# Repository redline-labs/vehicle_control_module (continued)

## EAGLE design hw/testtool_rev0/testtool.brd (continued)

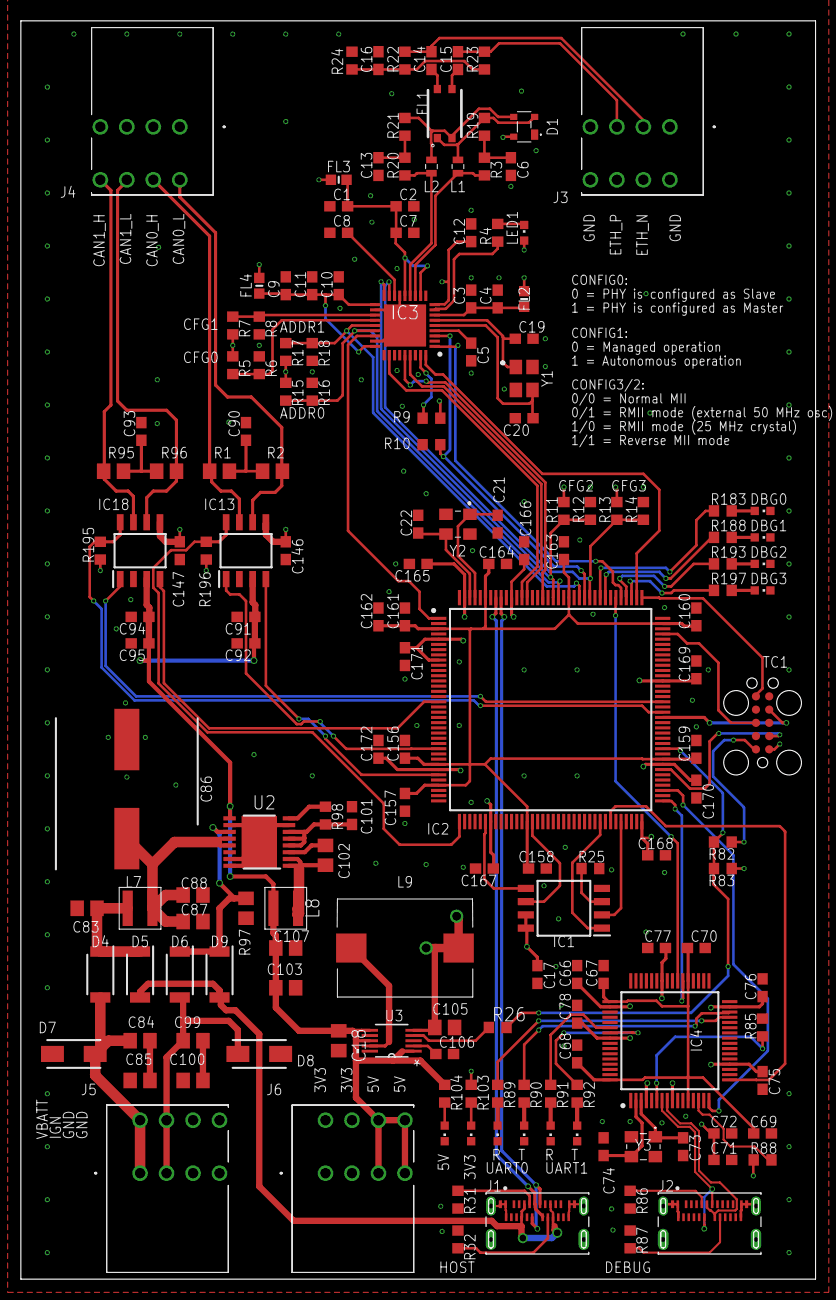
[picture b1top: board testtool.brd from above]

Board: 4 copper layers, 76.2 x 120.6 mm, 169 parts (0 on the bottom side), 113 nets.

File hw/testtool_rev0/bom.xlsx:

Parts | Qty | Value | Package | Device | Description | MANUFACTURER_NAME | MANUFACTURER_PART_NUMBER | MOUSER_PART_NUMBER
C1, C3, C9, C92, C95 | 5 | 10uF | C0603 | GRM188R6YA106MA73J | CAPACITOR, American symbol
C101 | 1 | 0.47uF | C0603 | C1608X7R1H474K080AC | CAPACITOR, American symbol
C102 | 1 | 220nF | C0805 | C0805X223K1RECAUTO | CAPACITOR, American symbol
C16, C90, C93 | 3 | 4.7nF | C0603 | C1608C0G2A472J080AE | CAPACITOR, American symbol
C18, C87, C103, C105, C107 | 5 | 10uF | C0805 | GRM21BC8YA106ME11L | CAPACITOR, American symbol
C19, C20 | 2 | 8.2pF | C0603 | GCM1885C2A8R2DA16D | CAPACITOR, American symbol
C2, C7, C10, C11, C14, C15, C17, C66, C68, C69, C70, C75, C76, C77, C78, C91, C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 | 34 | 100nF | C0603 | GCM1887U1H103JA16J | CAPACITOR, American symbol
C21, C22 | 2 | 12pF | C0603 | C0603C120K5GACTU | CAPACITOR, American symbol
C4, C5, C8, C12, C106, C162 | 6 | 1uF | C0603 | GMJ107CB7105MAHR | CAPACITOR, American symbol
C6, C13 | 2 | 47pF | C0603 | C0603C470J1GACAUTO | CAPACITOR, American symbol
C67 | 1 | 3.3uF | C0603 | C1608X5R1V335M080AC | CAPACITOR, American symbol
C71, C72, C165 | 3 | 4.7uF | C0603 | C1608JB1V475K080AC | CAPACITOR, American symbol
C73, C74 | 2 | 18nF | C0603 | GCM188R72A183KA37J | CAPACITOR, American symbol
C83, C88 | 2 | 0.47uF | C0805 | GCM21BR71H474KA55K | CAPACITOR, American symbol
C84, C85, C99, C100 | 4 | 470pF | C0805 | GCM21A5C2E471JX01D | CAPACITOR, American symbol
C86 | 1 | UCZ1K151MNQ1MS | CAPAE1360X1450N | UCZ1K151MNQ1MS | Aluminum Electrolytic Capacitors - SMD 80V 150UF 20% | Nichicon | UCZ1K151MNQ1MS | 647-UCZ1K151MNQ1MS
D1 | 1 | PESD2ETH-AXR | PESD2ETHAXR | PESD2ETH-AXR | ESD Suppressors / TVS Diodes PESD2ETH-AX/SOT4/REEL 7 Q3/T4" | Nexperia | PESD2ETH-AXR | 771-PESD2ETH-AXR
D4, D5, D6, D9 | 4 | PMEG3030EP,115 | SODFL4725X110N | PMEG3030EP,115 | Nexperia PMEG3030EP,115 SMT Schottky Diode, 30V 3A, 2-Pin SOD128 | Nexperia | PMEG3030EP,115 | 771-PMEG3030EP115
D7, D8 | 2 | SMAJ24CA-Q | DIONM5127X229N | SMAJ24CA-Q | Bourns SMAJ24CA-Q, Bi-Directional TVS Diode, 400W, 2-Pin DO-214AC | Bourns | SMAJ24CA-Q | 652-SMAJ24CA-Q
FL1 | 1 | ACT45L-201-2P-TL000 | ACT45L_1 | ACT45L-201-2P-TL000 | Common mode choke SMD 200uH 100mA 50V TDK ACT Series Shielded SMD Common Mode L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 | TDK | ACT45L-201-2P-TL000 | 810-ACT45L2012PTL000
FL2, FL3, FL4 | 3 | BLM18PG330SN1D | BEADC1608X95N | BLM18PG330SN1D | BLM18_N1D Series EMI Suppression Filter 33+/-25% at 100MHz 3A @85 | Murata Electronics | BLM18PG330SN1D | 81-BLM18PG330SN1D
IC1 | 1 | SST26VF032BT-104I_SM | SOIC127P794X203-8N | SST26VF032BT-104I_SM | Microchip Technology SST26VF032BT-104I/SM 32Mbit Flash Memory Chip, 8-Pin SOIJ | Microchip | SST26VF032BT-104I/SM | 579-T26VF032BT104ISM
IC13, IC18 | 2 | TLE9250XSJXUMA1 | SOIC127P602X173-8N | TLE9250XSJXUMA1 | CAN Interface IC TRANSCEIVER | Infineon | TLE9250XSJXUMA1 | 726-TLE9250XSJXUMA1
IC2 | 1 | ATSAMV71Q21B-AABT | QFP50P2200X2200X160-144N | ATSAMV71Q21B-AABT | ARM Microcontrollers - MCU 2MB FLASH 384KB SRAM LQFP144 T/R | Microchip | ATSAMV71Q21B-AABT | 579-ATSAMV71Q21BAABT
IC3 | 1 | TJA1100HNZ | QFN50P600X600X100-37N | TJA1100HNZ | NXP - TJA1100HNZ - ETHERNET PHY, AEC-Q100, 100MBPS, HVQFN36 | Nexperia | TJA1100HNZ | 771-TJA1100HNZ
IC4 | 1 | FT2232HL | QFP50P1200X1200X160-64N | FT2232HL | Dual High Speed USB UART/FIFO IC, LQFP64 FTDI Chip FT2232HL Dual UART Interface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 | FTDI Chip | FT2232HL
J1, J2 | 2 | 2305018-2 | TE_2305018-2 | 2305018-2 | TYPE C Right Angle Sealable SMT IPX8 3.1 GEN 2 Wire to Board USB | TE Connectivity
J3, J4, J5, J6 | 4 | TBL009-254-04GY-2GY | TBL00925404GY2GY | TBL009-254-04GY-2GY | Fixed Terminal Blocks Terminal block, screwless, 2.54, Horizontal, 4, Gray w Gr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 | CUI Devices | TBL009-254-04GY-2GY | 490-TBL00925404GY2GY
L1, L2 | 2 | 0603CS-R12XGLU | 0603CS82NXGLW | 0603CS-R12XGLU | COILCRAFT - 0603CS-R12XGLU - High Frequency Inductor, 120 nH, 0603CS Series, 30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 | COILCRAFT | 0603CS-R12XGLU | 994-0603CS-R12XGLU
L7 | 1 | XAL4020-102MEC | XAL40XX | XAL4020-102MEC | Fixed Inductors 1uH 20% 9.6A 14.60mOhms AEC-Q200 | COILCRAFT | XAL4020-102MEC | 994-XAL4020-102MEC
L8 | 1 | XAL4040-103MEC | XAL40XX | XAL4040-103MEC | Fixed Inductors XAL4040 High Current 10 uH 20 % 3.1 A | COILCRAFT | XAL4040-103MEC | 994-XAL4040-103MEC
L9 | 1 | DO3316P-103MLB | DO3316P103MLB | DO3316P-103MLB | Fixed Inductors DO3316P SMT Pwr Ind 10 uH 20 % 3.9 A | COILCRAFT | DO3316P-103MLB | 994-DO3316P-103MLB
LED1, LED4, LED5, LED6, LED7, LED11, LED12, LED13, LED14, LED15, LED16 | 11 |  | 0603 | 150060BS55040 | LED
R1, R2, R95, R96 | 4 | 60 | R0805 | ERJ-U06F60R4V | RESISTOR, American symbol
R24 | 1 | 100k | R0603 | SFR03EZPF1003 | RESISTOR, American symbol
R26, R82 | 2 | 0 | R0603 | RCS06030000Z0EC | RESISTOR, American symbol
R3, R19, R20, R21 | 4 | 49.9 | R0603 | ERJ-3EKF49R9V | RESISTOR, American symbol
R4, R22, R23 | 3 | 1k | R0603 |  | RESISTOR, American symbol
R5, R7, R10, R12, R13, R16, R18, R25, R83, R98, R103, R104, R183, R188, R193, R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 | 18 | 10k | R0603 |  | RESISTOR, American symbol
R6, R8, R11, R14, R15, R17 | 6 | DNP | R0603 |  | RESISTOR, American symbol
R85, R88, R89, R90, R91, R92 | 6 | 12k | R0603 | ERJ-PB3B1202V | RESISTOR, American symbol
R9, R31, R32, R86, R87 | 5 | 5.11k | R0603 | ERJ-S03F5111V | RESISTOR, American symbol
R97 | 1 | 1k | R0805 | ERJ-PB6B1001V | RESISTOR, American symbol
TC1 | 1 | TC2050-IDC | TC2050-IDC | TC2050-IDC | Tag-Connect In Circuit Programming & Debug Cable 10 Pin
U2 | 1 | LM63625 | PWP0016K_L | LM63625DQPWPRQ1 |  | Texas Instruments | LM63625DQPWPTQ1
U3 | 1 | TPS62007-Q1_DGS_10 | DGS10 | TPS62007-Q1_DGS_10 | Automotive Catalog High-Efficiency Step-Down Low Power DC-DC Converter | Texas Instruments | TPS62007-Q1_DGS_10
Y1 | 1 | NX3225SA-25MHZ-EXS00A-CS11338 | NX3225SA25MHZEXS00ACS11338 | NX3225SA-25MHZ-EXS00A-CS11338 | CRYSTAL 25MHZ 18PF SMD | NDK | NX3225SA-25MHZ-EXS00A-CS11338
Y2 | 1 | ABM8AIG-12.000MHZ-12-D2Z-T | ABM8AIG12000MHZ12D2ZT | ABM8AIG-12.000MHZ-12-D2Z-T | ABRACON - ABM8AIG-12.000MHZ-12-D2Z-T - CRYSTAL, AECQ200, 12MHZ, 12PF, 3.2X2.5MM | ABRACON | ABM8AIG-12.000MHz-12-D2Z-T | 815-ABM8AIG1212D2ZT
Y3 | 1 | ABM8AIG-12.000MHZ-1Z-T | ABM8AIG25000MHZ122ZT3 | ABM8AIG-12.000MHZ-1Z-T | Crystals 18pF 12MHz 10ppm AEC-Q200 -40C +125C | ABRACON | ABM8AIG-12.000MHZ-1Z-T | 815-M8AIG-12-1ZT

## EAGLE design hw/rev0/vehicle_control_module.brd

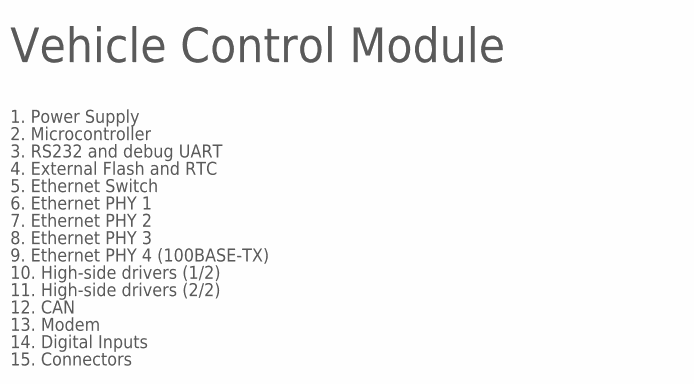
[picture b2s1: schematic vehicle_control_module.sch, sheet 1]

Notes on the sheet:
Vehicle Control Module
1. Power Supply
2. Microcontroller
3. RS232 and debug UART
4. External Flash and RTC
5. Ethernet Switch
6. Ethernet PHY 1
7. Ethernet PHY 2
8. Ethernet PHY 3
9. Ethernet PHY 4 (100BASE-TX)
10. High-side drivers (1/2)
12. CAN
13. Modem
15. Connectors
11. High-side drivers (2/2)
14. Digital Inputs

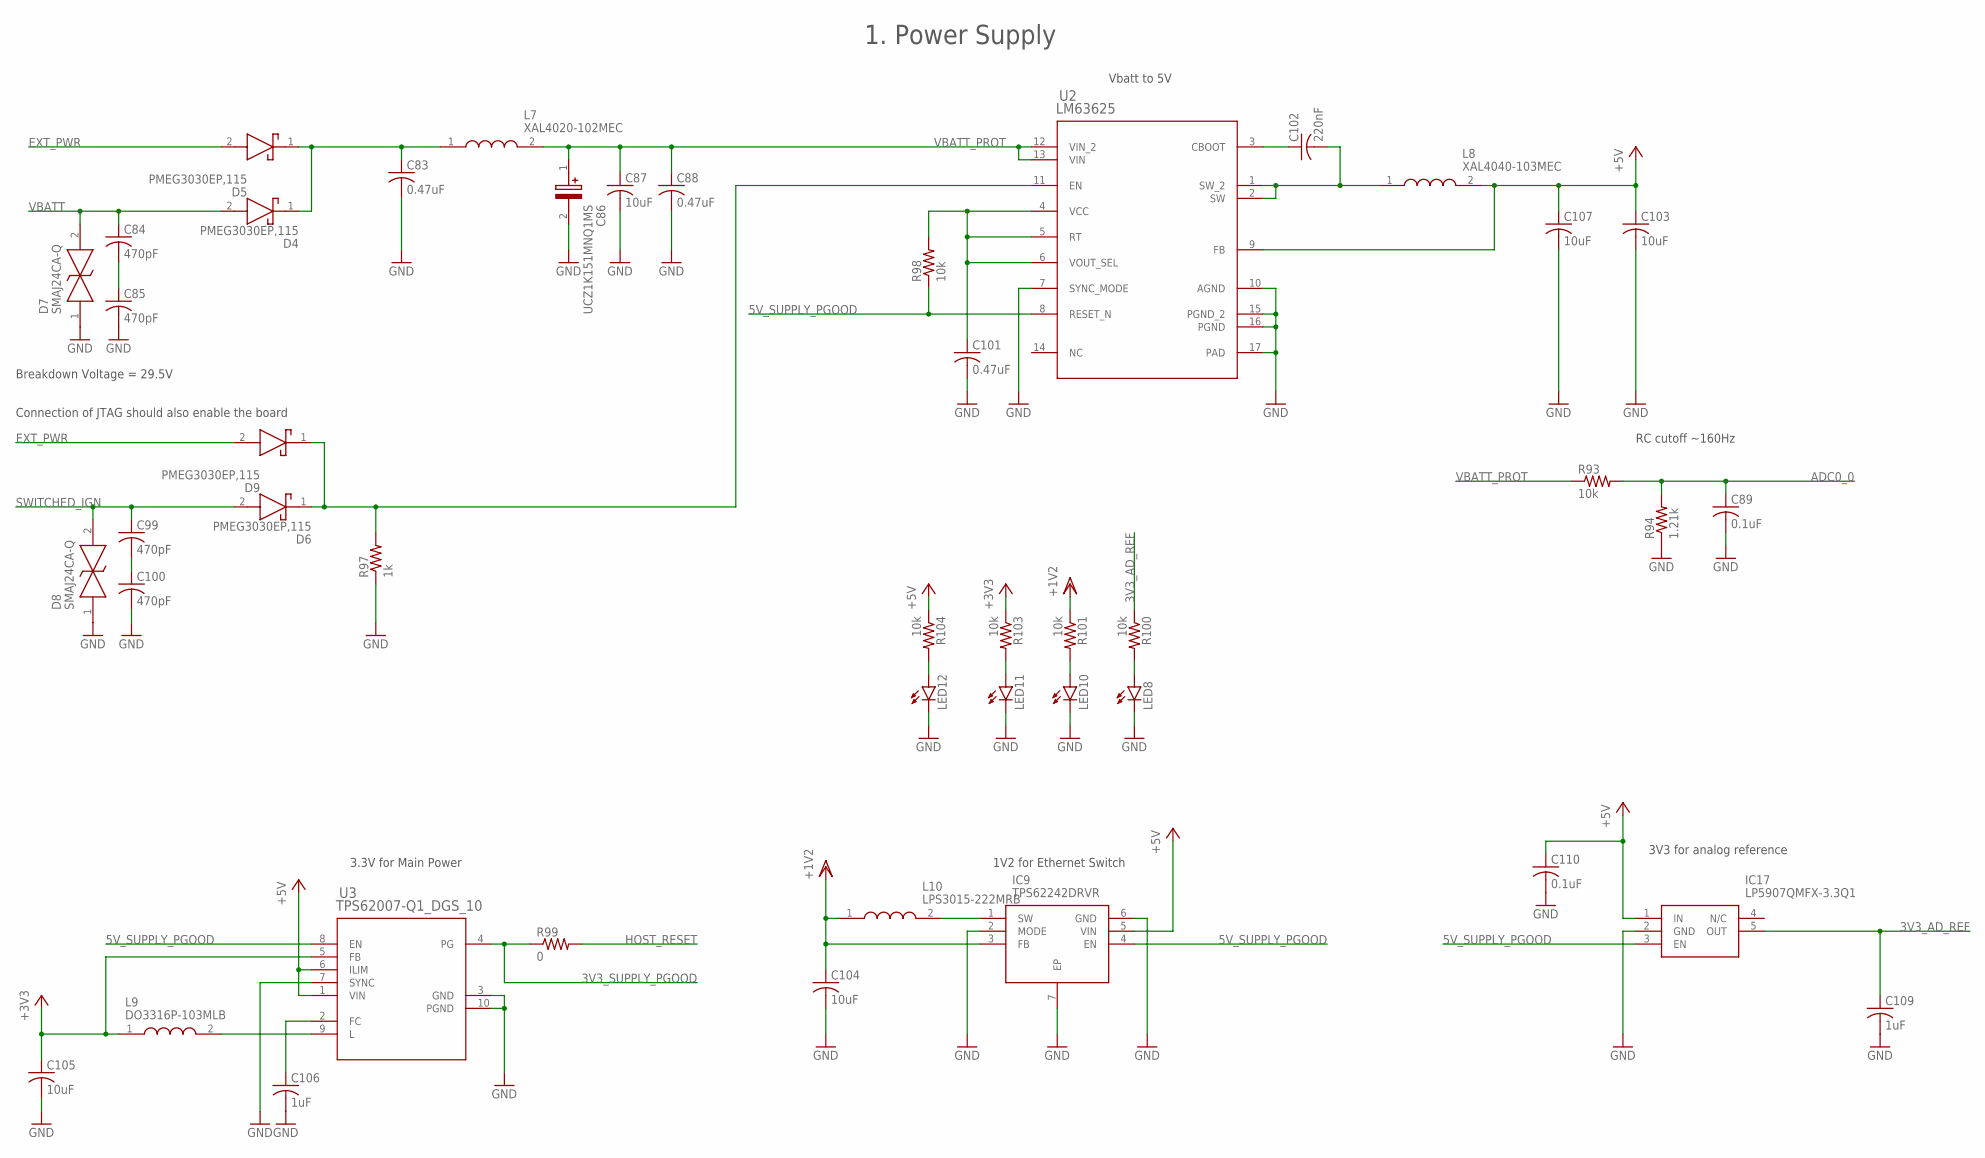
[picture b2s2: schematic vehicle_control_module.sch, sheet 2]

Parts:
C83, C88: 0.47uF; C0805
C84, C85, C99, C100: 470pF; C0805
C86: UCZ1K151MNQ1MS; CAPAE1360X1450N
C87, C103, C104, C105, C107: 10uF; C0805
C89, C110: 0.1uF; C0603
C101: 0.47uF; C0603
C102: 220nF; C0805
C106, C109: 1uF; C0603
D4, D5, D6, D9: PMEG3030EP,115; SODFL4725X110N
D7, D8: SMAJ24CA-Q; DIONM5127X229N
IC9: TPS62242DRVR; SON65P200X200X80-7N
IC17: LP5907QMFX-3.3Q1; SOT95P280X145-5N
L7: XAL4020-102MEC; XAL40XX
L8: XAL4040-103MEC; XAL40XX
L9: DO3316P-103MLB; DO3316P103MLB
L10: LPS3015-222MRB; LPS3015
LED8, LED10, LED11, LED12: LEDCHIPLED_0603; CHIPLED_0603
R93, R98, R100, R101, R103, R104: 10k; R0603
R94: 1.21k; R0603
R97: 1k; R0805
R99: 0; R0603
U2: LM63625; PWP0016K_L
U3: TPS62007-Q1_DGS_10; DGS10

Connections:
3V3_AD_REF: C109.1, IC17.5 (OUT), R100.1; also elsewhere on the board
3V3_SUPPLY_PGOOD: R99.1, U3.4 (PG)
5V_SUPPLY_PGOOD: IC9.4 (EN), IC17.3 (EN), R98.1, U2.8 (RESET_N), U3.8 (EN)
+3V3: C105.1, L9.1, R103.1, U3.5 (FB); also elsewhere on the board
+5V: C103.1, C107.1, C110.1, IC9.5 (VIN), IC17.1 (IN), L8.2, R104.1, U2.9 (FB), U3.1 (VIN), U3.6 (ILIM); also elsewhere on the board
ADC0_0: C89.1, R93.2, R94.2; also elsewhere on the board
EXT_PWR: D5.2 (A), D9.2 (A); also elsewhere on the board
GND: C83.2, C85.2, C86.2 (-), C87.2, C88.2, C89.2, C100.2, C101.2, C103.2, C104.2, C105.2, C106.2, C107.2, C109.2, C110.2, D7.1, D8.1, IC9.2 (MODE), IC9.6 (GND), IC9.7 (EP), IC17.2 (GND), LED8.C, LED10.C, LED11.C, LED12.C, R94.1, R97.1, U2.7 (SYNC_MODE), U2.10 (AGND), U2.15 (PGND_2), U2.16 (PGND), U2.17 (PAD), U3.3 (GND), U3.7 (SYNC), U3.10 (PGND); also elsewhere on the board
HOST_RESET: R99.2; also elsewhere on the board
unnamed: C99.2, C100.1
unnamed: D6.1 (K), D9.1 (K), R97.2, U2.11 (EN)
unnamed: C83.1, D4.1 (K), D5.1 (K), L7.1
unnamed: C84.2, C85.1
unnamed: C101.1, R98.2, U2.4 (VCC), U2.5 (RT), U2.6 (VOUT_SEL)
unnamed: L9.2, U3.9 (L)
unnamed: C102.2, L8.1, U2.1 (SW_2), U2.2 (SW)
unnamed: C106.1, U3.2 (FC)
unnamed: C102.1, U2.3 (CBOOT)
unnamed: LED8.A, R100.2
unnamed: IC9.1 (SW), L10.2
unnamed: LED10.A, R101.2
unnamed: LED11.A, R103.2
unnamed: LED12.A, R104.2
SWITCHED_IGN: C99.1, D6.2 (A), D8.2
VBATT: C84.1, D4.2 (A), D7.2; also elsewhere on the board
VBATT_PROT: C86.1 (+), C87.1, C88.1, L7.2, R93.1, U2.12 (VIN_2), U2.13 (VIN)
VDD: C104.1, IC9.3 (FB), L10.1, R101.1; also elsewhere on the board

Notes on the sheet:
1. Power Supply
1V2 for Ethernet Switch
Vbatt to 5V
3.3V for Main Power
3V3 for analog reference
Breakdown Voltage = 29.5V
RC cutoff ~160Hz
Connection of JTAG should also enable the board

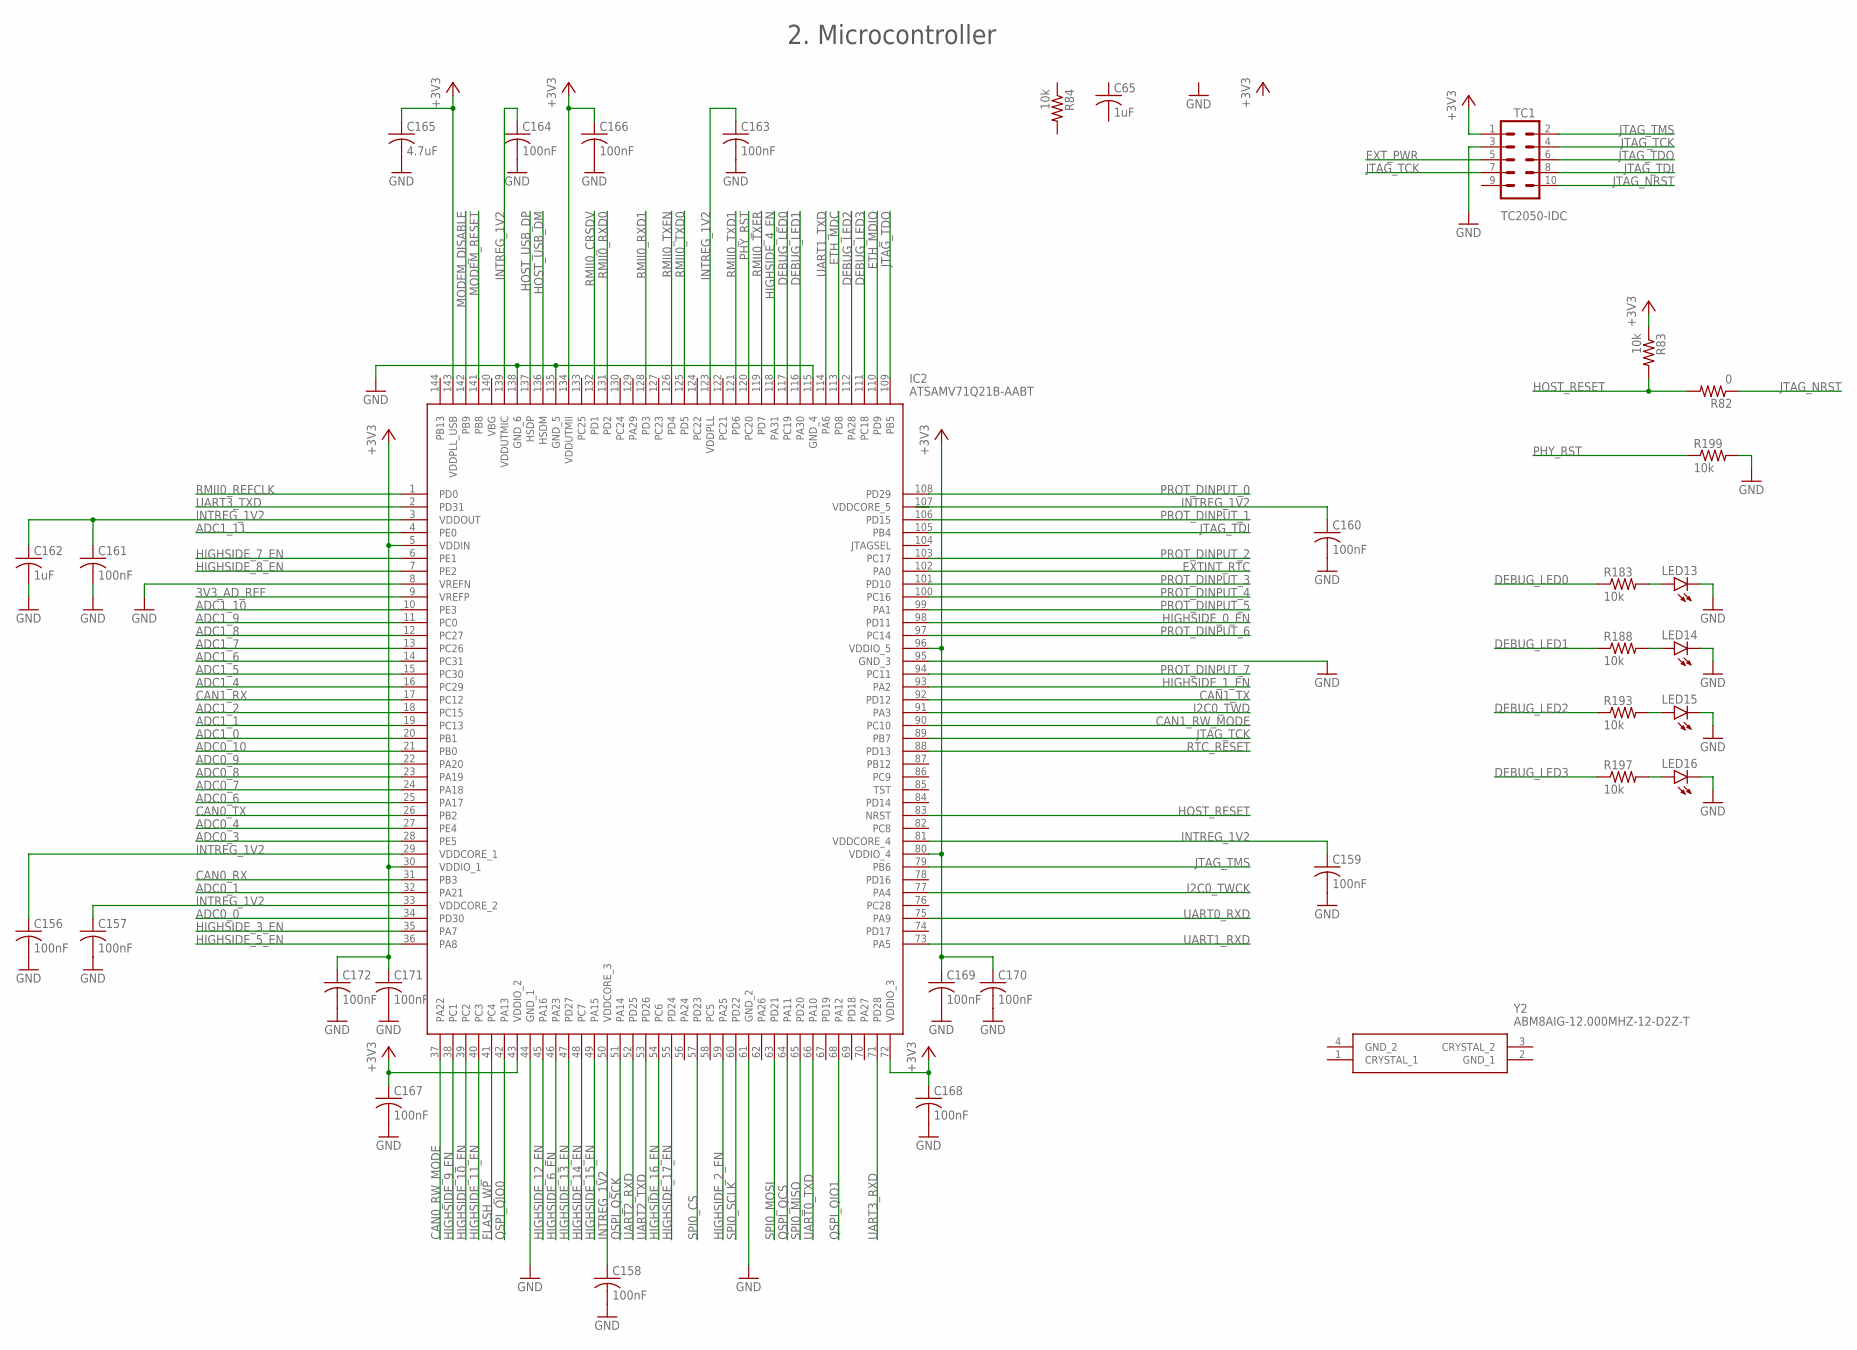
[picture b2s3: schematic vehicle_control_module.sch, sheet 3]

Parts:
C65, C162: 1uF; C0603
C156, C157, C158, C159, C160, C161, C163, C164, C166, C167, C168, C169, C170, C171, C172: 100nF; C0603
C165: 4.7uF; C0603
IC2: ATSAMV71Q21B-AABT; QFP50P2200X2200X160-144N
LED13, LED14, LED15, LED16: LEDCHIPLED_0603; CHIPLED_0603
R82: 0; R0603
R83, R84, R183, R188, R193, R197, R199: 10k; R0603
TC1: TC2050-IDC
Y2: ABM8AIG-12.000MHZ-12-D2Z-T; ABM8AIG12000MHZ12D2ZT

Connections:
3V3_AD_REF: IC2.9 (VREFP); also elsewhere on the board
+3V3: C165.1, C166.1, C167.1, C168.1, C169.1, C170.1, C171.1, C172.1, IC2.5 (VDDIN), IC2.30 (VDDIO_1), IC2.43 (VDDIO_2), IC2.72 (VDDIO_3), IC2.80 (VDDIO_4), IC2.96 (VDDIO_5), IC2.134 (VDDUTMII), IC2.143 (VDDPLL_USB), R83.1, TC1.1; also elsewhere on the board
ADC0_0: IC2.34 (PD30); also elsewhere on the board
ADC0_1: IC2.32 (PA21)
ADC0_3: IC2.28 (PE5); also elsewhere on the board
ADC0_4: IC2.27 (PE4); also elsewhere on the board
ADC0_6: IC2.25 (PA17); also elsewhere on the board
ADC0_7: IC2.24 (PA18); also elsewhere on the board
ADC0_8: IC2.23 (PA19); also elsewhere on the board
ADC0_9: IC2.22 (PA20); also elsewhere on the board
ADC0_10: IC2.21 (PB0); also elsewhere on the board
ADC1_0: IC2.20 (PB1); also elsewhere on the board
ADC1_1: IC2.19 (PC13); also elsewhere on the board
ADC1_2: IC2.18 (PC15); also elsewhere on the board
ADC1_4: IC2.16 (PC29); also elsewhere on the board
ADC1_5: IC2.15 (PC30); also elsewhere on the board
ADC1_6: IC2.14 (PC31); also elsewhere on the board
ADC1_7: IC2.13 (PC26); also elsewhere on the board
ADC1_8: IC2.12 (PC27); also elsewhere on the board
ADC1_9: IC2.11 (PC0); also elsewhere on the board
ADC1_10: IC2.10 (PE3); also elsewhere on the board
ADC1_11: IC2.4 (PE0); also elsewhere on the board
CAN0_RW_MODE: IC2.37 (PA22); also elsewhere on the board
CAN0_RX: IC2.31 (PB3); also elsewhere on the board
CAN0_TX: IC2.26 (PB2); also elsewhere on the board
CAN1_RW_MODE: IC2.90 (PC10); also elsewhere on the board
CAN1_RX: IC2.17 (PC12); also elsewhere on the board
CAN1_TX: IC2.92 (PD12); also elsewhere on the board
DEBUG_LED0: IC2.117 (PC19), R183.1
DEBUG_LED1: IC2.116 (PA30), R188.1
DEBUG_LED2: IC2.112 (PA28), R193.1
DEBUG_LED3: IC2.111 (PC18), R197.1
ETH_MDC: IC2.113 (PD8); also elsewhere on the board
ETH_MDIO: IC2.110 (PD9); also elsewhere on the board
EXTINT_RTC: IC2.102 (PA0); also elsewhere on the board
EXT_PWR: TC1.5; also elsewhere on the board
FLASH_WP: IC2.41 (PC4); also elsewhere on the board
GND: C156.2, C157.2, C158.2, C159.2, C160.2, C161.2, C162.2, C163.2, C164.2, C165.2, C166.2, C167.2, C168.2, C169.2, C170.2, C171.2, C172.2, IC2.8 (VREFN), IC2.44 (GND_1), IC2.61 (GND_2), IC2.95 (GND_3), IC2.115 (GND_4), IC2.135 (GND_5), IC2.138 (GND_6), LED13.C, LED14.C, LED15.C, LED16.C, R199.2, TC1.3; also elsewhere on the board
HIGHSIDE_0_EN: IC2.98 (PD11); also elsewhere on the board
HIGHSIDE_1_EN: IC2.93 (PA2); also elsewhere on the board
HIGHSIDE_2_EN: IC2.59 (PA25); also elsewhere on the board
HIGHSIDE_3_EN: IC2.35 (PA7); also elsewhere on the board
HIGHSIDE_4_EN: IC2.118 (PA31); also elsewhere on the board
HIGHSIDE_5_EN: IC2.36 (PA8); also elsewhere on the board
HIGHSIDE_6_EN: IC2.46 (PA23); also elsewhere on the board
HIGHSIDE_7_EN: IC2.6 (PE1); also elsewhere on the board
HIGHSIDE_8_EN: IC2.7 (PE2); also elsewhere on the board
HIGHSIDE_9_EN: IC2.38 (PC1); also elsewhere on the board
HIGHSIDE_10_EN: IC2.39 (PC2); also elsewhere on the board
HIGHSIDE_11_EN: IC2.40 (PC3); also elsewhere on the board
HIGHSIDE_12_EN: IC2.45 (PA16); also elsewhere on the board
HIGHSIDE_13_EN: IC2.47 (PD27); also elsewhere on the board
HIGHSIDE_14_EN: IC2.48 (PC7); also elsewhere on the board
HIGHSIDE_15_EN: IC2.49 (PA15); also elsewhere on the board
HIGHSIDE_16_EN: IC2.54 (PC6); also elsewhere on the board
HIGHSIDE_17_EN: IC2.55 (PD24); also elsewhere on the board
HOST_RESET: IC2.83 (NRST), R82.2, R83.2; also elsewhere on the board
HOST_USB_DM: IC2.136 (HSDM); also elsewhere on the board
HOST_USB_DP: IC2.137 (HSDP); also elsewhere on the board
I2C0_TWCK: IC2.77 (PA4); also elsewhere on the board
I2C0_TWD: IC2.91 (PA3); also elsewhere on the board
INTREG_1V2: C156.1, C157.1, C158.1, C159.1, C160.1, C161.1, C162.1, C163.1, C164.1, IC2.3 (VDDOUT), IC2.29 (VDDCORE_1), IC2.33 (VDDCORE_2), IC2.50 (VDDCORE_3), IC2.81 (VDDCORE_4), IC2.107 (VDDCORE_5), IC2.123 (VDDPLL), IC2.139 (VDDUTMIC)
JTAG_NRST: R82.1, TC1.10
JTAG_TCK: IC2.89 (PB7), TC1.4, TC1.7
JTAG_TDI: IC2.105 (PB4), TC1.8
JTAG_TDO: IC2.109 (PB5), TC1.6
JTAG_TMS: IC2.79 (PB6), TC1.2
MODEM_DISABLE: IC2.142 (PB9); also elsewhere on the board
MODEM_RESET: IC2.141 (PB8); also elsewhere on the board
unnamed: LED13.A, R183.2
unnamed: LED14.A, R188.2
unnamed: LED15.A, R193.2
unnamed: LED16.A, R197.2
PHY_RST: IC2.120 (PC20), R199.1; also elsewhere on the board
PROT_DINPUT_0: IC2.108 (PD29); also elsewhere on the board
PROT_DINPUT_1: IC2.106 (PD15); also elsewhere on the board
PROT_DINPUT_2: IC2.103 (PC17); also elsewhere on the board
PROT_DINPUT_3: IC2.101 (PD10); also elsewhere on the board
PROT_DINPUT_4: IC2.100 (PC16); also elsewhere on the board
PROT_DINPUT_5: IC2.99 (PA1); also elsewhere on the board
PROT_DINPUT_6: IC2.97 (PC14); also elsewhere on the board
PROT_DINPUT_7: IC2.94 (PC11); also elsewhere on the board
QSPI_QCS: IC2.64 (PA11); also elsewhere on the board
QSPI_QIO0: IC2.42 (PA13); also elsewhere on the board
QSPI_QIO1: IC2.68 (PA12); also elsewhere on the board
QSPI_QSCK: IC2.51 (PA14); also elsewhere on the board
RMII0_CRSDV: IC2.132 (PD1); also elsewhere on the board
RMII0_REFCLK: IC2.1 (PD0); also elsewhere on the board
RMII0_RXD0: IC2.131 (PD2); also elsewhere on the board
RMII0_RXD1: IC2.128 (PD3); also elsewhere on the board
RMII0_TXD0: IC2.125 (PD5); also elsewhere on the board
RMII0_TXD1: IC2.121 (PD6); also elsewhere on the board
RMII0_TXEN: IC2.126 (PD4); also elsewhere on the board
RMII0_TXER: IC2.119 (PD7); also elsewhere on the board
RTC_RESET: IC2.88 (PD13); also elsewhere on the board
SPI0_CS: IC2.57 (PD23); also elsewhere on the board
SPI0_MISO: IC2.65 (PD20); also elsewhere on the board
SPI0_MOSI: IC2.63 (PD21); also elsewhere on the board
SPI0_SCLK: IC2.60 (PD22); also elsewhere on the board
UART0_RXD: IC2.75 (PA9); also elsewhere on the board
UART0_TXD: IC2.66 (PA10); also elsewhere on the board
UART1_RXD: IC2.73 (PA5); also elsewhere on the board
UART1_TXD: IC2.114 (PA6); also elsewhere on the board
UART2_RXD: IC2.52 (PD25); also elsewhere on the board
UART2_TXD: IC2.53 (PD26); also elsewhere on the board
UART3_RXD: IC2.71 (PD28); also elsewhere on the board
UART3_TXD: IC2.2 (PD31); also elsewhere on the board

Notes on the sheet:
2. Microcontroller

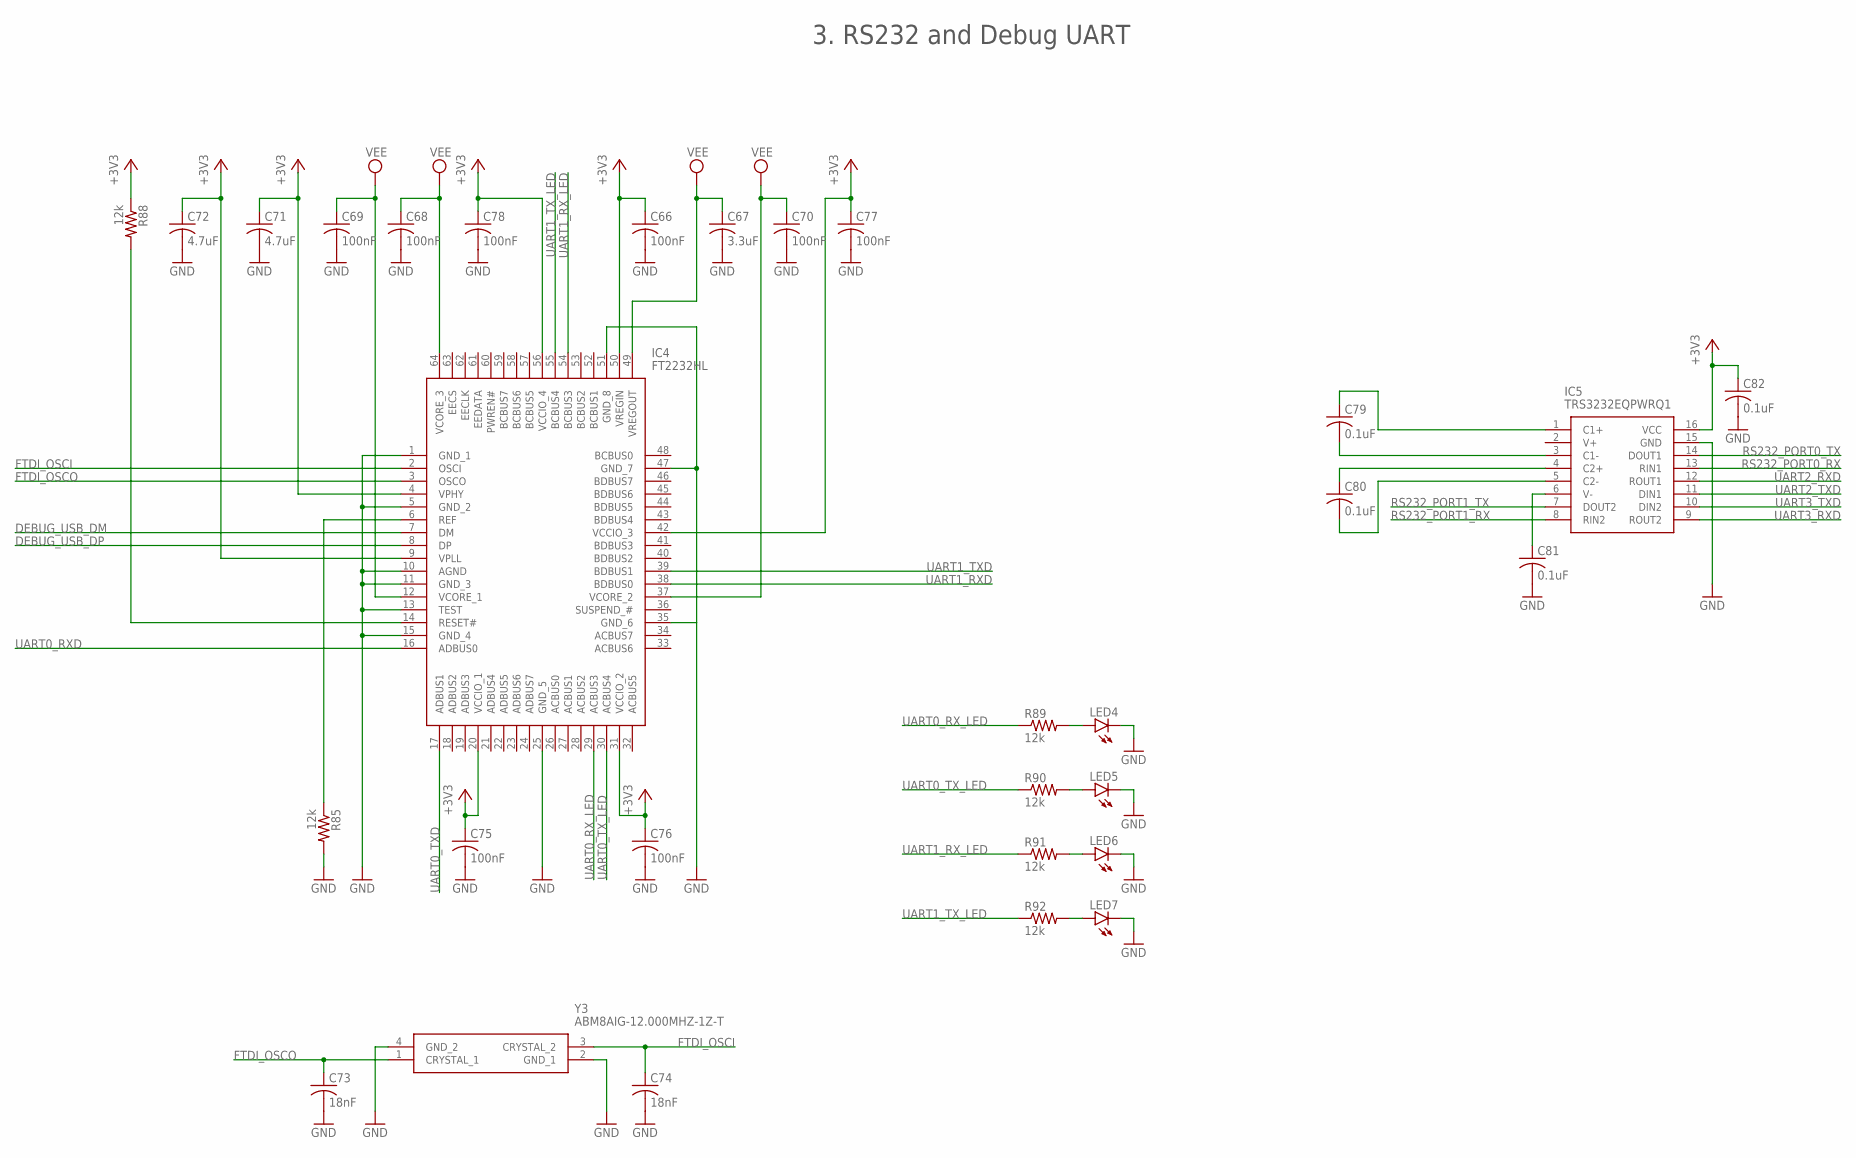
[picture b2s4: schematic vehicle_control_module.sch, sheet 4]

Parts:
C66, C68, C69, C70, C75, C76, C77, C78: 100nF; C0603
C67: 3.3uF; C0603
C71, C72: 4.7uF; C0603
C73, C74: 18nF; C0603
C79, C80, C81, C82: 0.1uF; C0603
IC4: FT2232HL; QFP50P1200X1200X160-64N
IC5: TRS3232EQPWRQ1; SOP65P640X120-16N
LED4, LED5, LED6, LED7: LEDCHIPLED_0603; CHIPLED_0603
R85, R88, R89, R90, R91, R92: 12k; R0603
Y3: ABM8AIG-12.000MHZ-1Z-T; ABM8AIG25000MHZ122ZT3

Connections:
+3V3: C66.1, C71.1, C72.1, C75.1, C76.1, C77.1, C78.1, C82.1, IC4.4 (VPHY), IC4.9 (VPLL), IC4.20 (VCCIO_1), IC4.31 (VCCIO_2), IC4.42 (VCCIO_3), IC4.50 (VREGIN), IC4.56 (VCCIO_4), IC5.16 (VCC), R88.1; also elsewhere on the board
DEBUG_USB_DM: IC4.7 (DM); also elsewhere on the board
DEBUG_USB_DP: IC4.8 (DP); also elsewhere on the board
FTDI_OSCI: C74.1, IC4.2 (OSCI), Y3.3 (CRYSTAL_2)
FTDI_OSCO: C73.1, IC4.3 (OSCO), Y3.1 (CRYSTAL_1)
GND: C66.2, C67.2, C68.2, C69.2, C70.2, C71.2, C72.2, C73.2, C74.2, C75.2, C76.2, C77.2, C78.2, C81.2, C82.2, IC4.1 (GND_1), IC4.5 (GND_2), IC4.10 (AGND), IC4.11 (GND_3), IC4.13 (TEST), IC4.15 (GND_4), IC4.25 (GND_5), IC4.35 (GND_6), IC4.47 (GND_7), IC4.51 (GND_8), IC5.15 (GND), LED4.C, LED5.C, LED6.C, LED7.C, R85.2, Y3.2 (GND_1), Y3.4 (GND_2); also elsewhere on the board
unnamed: IC4.6 (REF), R85.1
unnamed: IC4.14 (RESET#), R88.2
unnamed: LED5.A, R90.2
unnamed: LED4.A, R89.2
unnamed: LED6.A, R91.2
unnamed: LED7.A, R92.2
unnamed: C79.1, IC5.1 (C1+)
unnamed: C79.2, IC5.3 (C1-)
unnamed: C80.1, IC5.4 (C2+)
unnamed: C80.2, IC5.5 (C2-)
unnamed: C81.1, IC5.6 (V-)
RS232_PORT0_RX: IC5.13 (RIN1); also elsewhere on the board
RS232_PORT0_TX: IC5.14 (DOUT1); also elsewhere on the board
RS232_PORT1_RX: IC5.8 (RIN2); also elsewhere on the board
RS232_PORT1_TX: IC5.7 (DOUT2); also elsewhere on the board
UART0_RXD: IC4.16 (ADBUS0); also elsewhere on the board
UART0_RX_LED: IC4.29 (ACBUS3), R89.1
UART0_TXD: IC4.17 (ADBUS1); also elsewhere on the board
UART0_TX_LED: IC4.30 (ACBUS4), R90.1
UART1_RXD: IC4.38 (BDBUS0); also elsewhere on the board
UART1_RX_LED: IC4.54 (BCBUS3), R91.1
UART1_TXD: IC4.39 (BDBUS1); also elsewhere on the board
UART1_TX_LED: IC4.55 (BCBUS4), R92.1
UART2_RXD: IC5.12 (ROUT1); also elsewhere on the board
UART2_TXD: IC5.11 (DIN1); also elsewhere on the board
UART3_RXD: IC5.9 (ROUT2); also elsewhere on the board
UART3_TXD: IC5.10 (DIN2); also elsewhere on the board
VEE: C67.1, C68.1, C69.1, C70.1, IC4.12 (VCORE_1), IC4.37 (VCORE_2), IC4.49 (VREGOUT), IC4.64 (VCORE_3)

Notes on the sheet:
3. RS232 and Debug UART

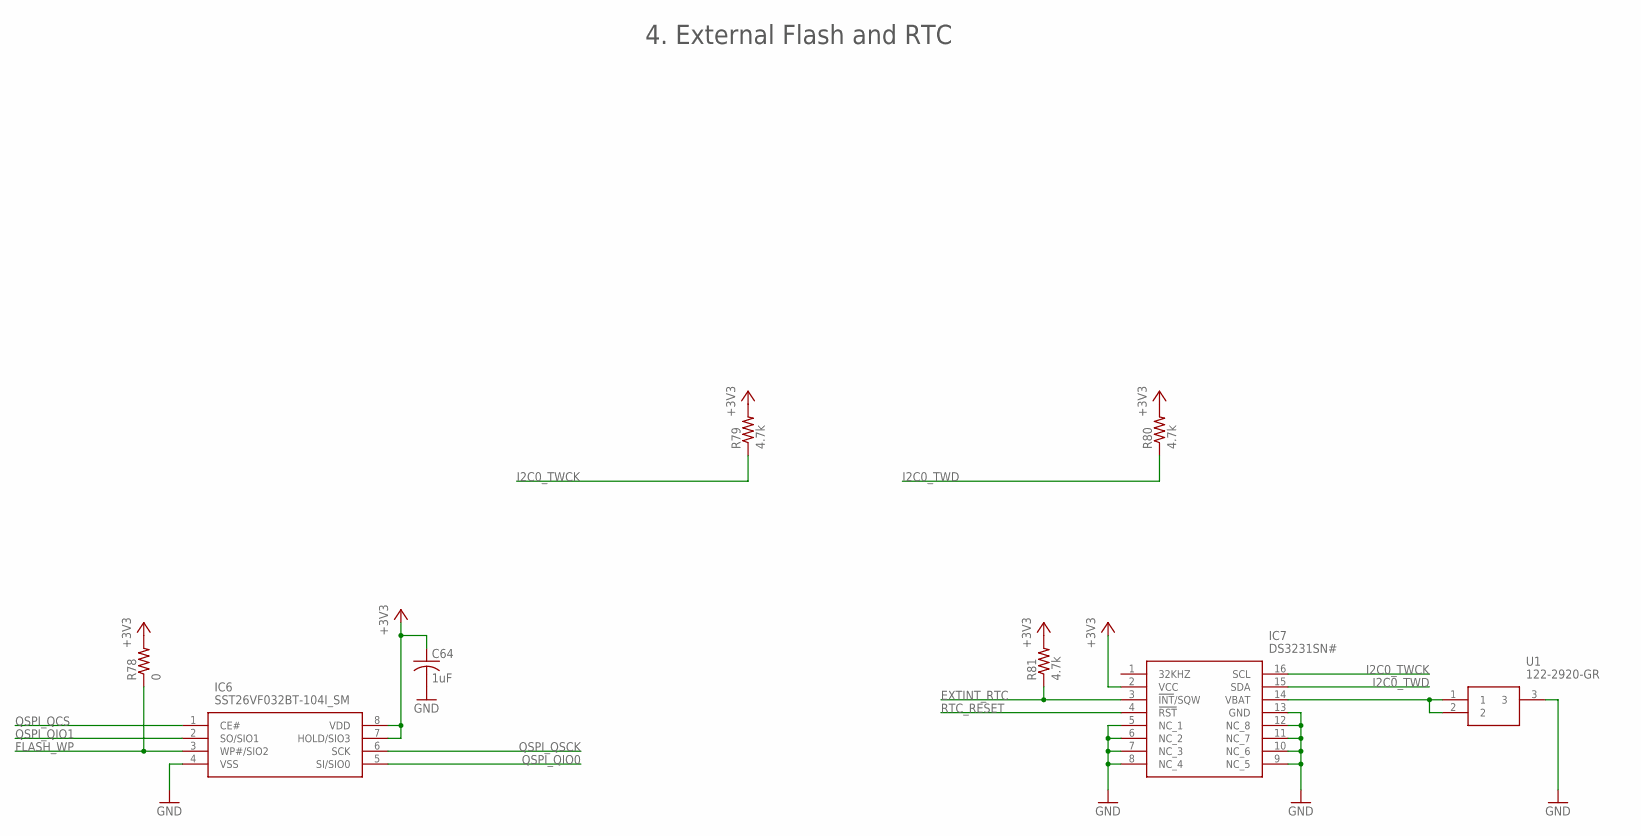
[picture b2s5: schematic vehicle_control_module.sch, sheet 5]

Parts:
C64: 1uF; C0603
IC6: SST26VF032BT-104I_SM; SOIC127P794X203-8N
IC7: DS3231SN#; SOIC127P1032X265-16N
R78: 0; R0603
R79, R80, R81: 4.7k; R0603
U1: 122-2920-GR; 1222920GR

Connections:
+3V3: C64.1, IC6.7 (HOLD/SIO3), IC6.8 (VDD), IC7.2 (VCC), R78.2, R79.2, R80.2, R81.2; also elsewhere on the board
EXTINT_RTC: IC7.3 (!INT!/SQW), R81.1; also elsewhere on the board
FLASH_WP: IC6.3 (WP#/SIO2), R78.1; also elsewhere on the board
GND: C64.2, IC6.4 (VSS), IC7.5 (NC_1), IC7.6 (NC_2), IC7.7 (NC_3), IC7.8 (NC_4), IC7.9 (NC_5), IC7.10 (NC_6), IC7.11 (NC_7), IC7.12 (NC_8), IC7.13 (GND), U1.3; also elsewhere on the board
I2C0_TWCK: IC7.16 (SCL), R79.1; also elsewhere on the board
I2C0_TWD: IC7.15 (SDA), R80.1; also elsewhere on the board
unnamed: IC7.14 (VBAT), U1.1, U1.2
QSPI_QCS: IC6.1 (CE#); also elsewhere on the board
QSPI_QIO0: IC6.5 (SI/SIO0); also elsewhere on the board
QSPI_QIO1: IC6.2 (SO/SIO1); also elsewhere on the board
QSPI_QSCK: IC6.6 (SCK); also elsewhere on the board
RTC_RESET: IC7.4 (!RST); also elsewhere on the board

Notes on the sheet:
4. External Flash and RTC
